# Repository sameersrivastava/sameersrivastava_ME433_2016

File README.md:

# sameersrivastava_ME433_2016
ME 433 Github Repository

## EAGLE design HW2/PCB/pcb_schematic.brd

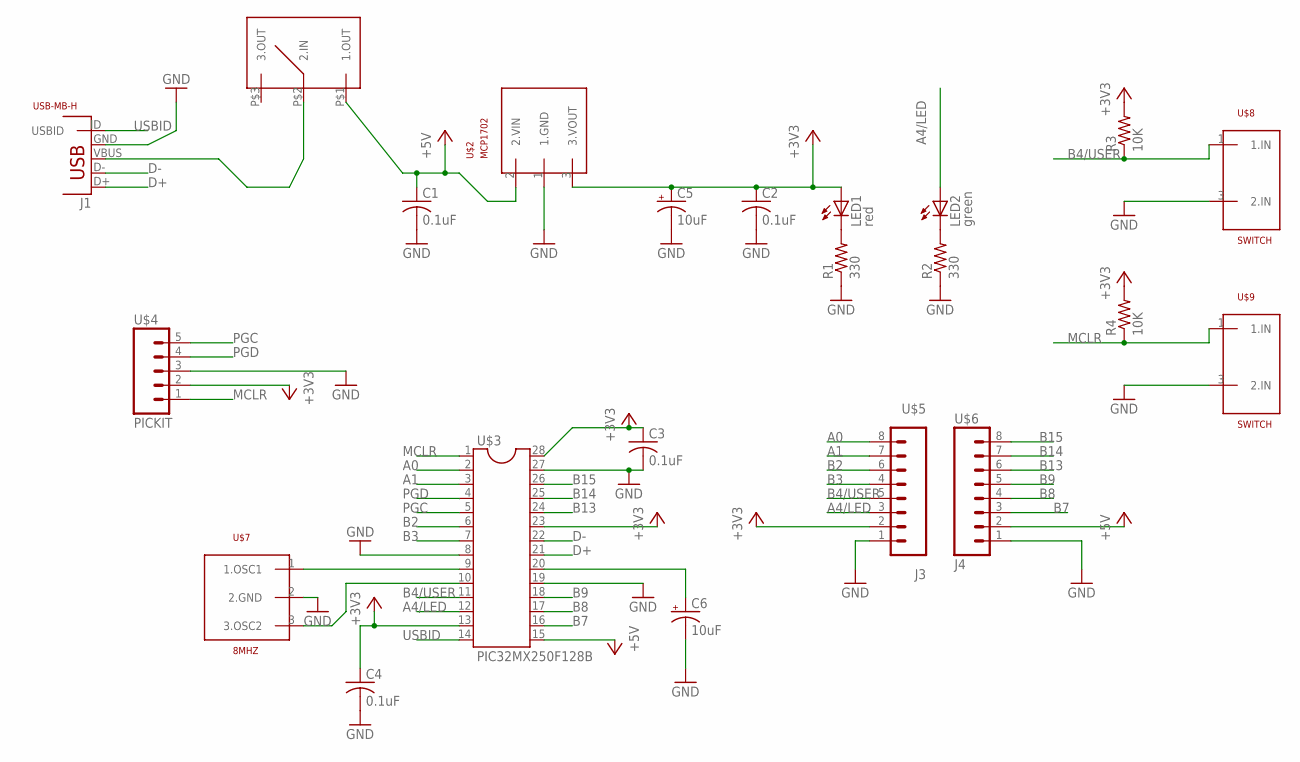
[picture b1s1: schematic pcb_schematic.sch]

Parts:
C1, C2, C3, C4: 0.1uF; C025-025X050
C5, C6: 10uF; B45181A
J1: USB-MB-H
LED1: red; LED3MM
LED2: green; LED3MM
R1, R2: 330; 0204/7
R3, R4: 10K; 0204/7
U$1: SLIDE_SWITCH
U$2: MCP1702; TO92
U$3: PIC32MX250F128B
U$4: PICKIT
U$5: J3
U$6: J4
U$7: 8MHZ
U$8, U$9: SWITCH

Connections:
+3V3: C2.1, C3.1, C4.1, C5.+, LED1.A, R3.2, R4.2, U$2.3 (3.VOUT), U$3.13 (13.VDD), U$3.23 (23.VUSB3V3), U$3.28 (28.AVDD), U$4.2 (2.3V3), U$5.2 (2.3V3)
+5V: C1.1, U$1.P$1 (1.OUT), U$2.2 (2.VIN), U$3.15 (15.VBUS), U$6.2 (2.5V)
A0: U$3.2 (2.A0), U$5.8 (8.A0)
A1: U$3.3 (3.A1), U$5.7 (7.A1)
A4/LED: LED2.A, U$3.12 (12.A4/LED), U$5.3 (3.A4/LED)
B2: U$3.6 (6.B2), U$5.6 (5.B3)
B3: U$3.7 (7.B3), U$5.4 (4.B4/USER)
B4/USER: R3.1, U$3.11 (11.B4/USER), U$5.5, U$8.1 (1.IN)
B7: U$3.16 (16.B7), U$6.3 (3.B7)
B8: U$3.17 (17.B8), U$6.4 (4.B8)
B9: U$3.18 (18.B9), U$6.5 (5.B9)
B13: U$3.24 (24.B13), U$6.6 (6.B13)
B14: U$3.25 (25.B14), U$6.7 (7.B14)
B15: U$3.26 (26.B15), U$6.8 (8.B15)
D+: J1.D+, U$3.21 (21.D+/B10)
D-: J1.D-, U$3.22 (22.D-/B11)
GND: C1.2, C2.2, C3.2, C4.2, C5.-, C6.-, J1.GND, R1.1, R2.1, U$2.1 (1.GND), U$3.8 (8.GND), U$3.19 (19.VSS), U$3.27 (27.AVSS), U$4.3 (3.GND), U$5.1 (1.GND), U$6.1 (1.GND), U$7.2 (2.GND), U$8.3 (2.IN), U$9.3 (2.IN)
MCLR: R4.1, U$3.1 (1.MCLR), U$4.1 (1.MCLR), U$9.1 (1.IN)
unnamed: J1.VBUS, U$1.P$2 (2.IN)
unnamed: LED1.K (C), R1.2
unnamed: LED2.K (C), R2.2
unnamed: U$3.9 (9.OSC1), U$7.1 (1.OSC1)
unnamed: U$3.10 (10.OSC2), U$7.3 (3.OSC2)
unnamed: C6.+, U$3.20 (20.VCAP)
PGC: U$3.5 (5.PGC), U$4.5 (5.PGC)
PGD: U$3.4 (4.PGD), U$4.4 (4.PGD)
USBID: J1.ID (USBID), U$3.14 (14.USBID/B5)

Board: 2 copper layers, 22 parts (0 on the bottom side), 27 nets, no tracks yet.

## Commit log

2016-04-05 Adding first commit of HW1 project with main.c
2016-04-05 .gitignore to .DS_Store. Moved HW1.X into HW1. Added a picture of the circuit diagram as well.
2016-04-05 Renamed circuit diagram to fit convention. Added picture of breadboard for number 6.
2016-04-07 Added oscillations for number 2 for hw1.
2016-04-07 Added schematic and library is mostly finished.
2016-04-12 Completed more components for the pic and added it to the library.
2016-04-14 Added the voltage regulator and the usb with the usbid pin connected to the library.
2016-04-14 Added PIC32 to the library.
2016-04-14 Added the 8MHz resonator
2016-04-14 Added the PICKit.
2016-04-14 Added J3 (The first set of connectors).
2016-04-14 Added J4 to the library now.
2016-04-14 Added the slide switch.
2016-04-14 Started the schematic. Do not have the buttons in the library.
2016-04-14 Started the schematic. Need to add nets.
2016-04-14 Finished a good bit of the schematic.
2016-04-14 Finished schematic minus the buttons. Not sure what to do about those still.
2016-04-14 Started board.
2016-04-16 more schematic stuff here.
2016-04-16 Fixed pragma values in main.c
2016-04-16 Fixed pragma values to correct values.
2016-04-16 Made B4 into an input for button and A4 into ouput for LED.
2016-04-16 Added code to switch between LED on and off for 0.5ms
2016-04-16 Added button input to pause the program.
2016-04-21 PCB is closer.
2016-04-28 Just updating things.
2016-04-28 Added project HW4.
2016-04-28 Took spi-example and put it into main.c
2016-05-03 Added PIC32.h file to have all the configurations for the PIC32.h
2016-05-03 Added PIC32.h to the main.c and worked fine. Started to rewrite functions to communicate over SPI1.
2016-05-03 Added setVoltage function, but need to check if this works. working on the main function.
2016-05-03 Got a successful compile on to the PIC.
2016-05-05 Just committing some automatic changes from MPLAB IDE.
2016-05-05 Starting Project 5. Added the LCD programs.
2016-05-05 Added the initialization steps, but nothing is working as of now.
2016-05-05 got something to work....
2016-05-05 Added a line.
2016-05-05 Getting closer.
2016-05-05 working
2016-05-05 Got it to print the hwk.
2016-05-05 Picture of hwk.
2016-05-10 Can write continous text to the screen for HW5.
2016-05-10 Started HW6/=.
2016-05-12 Got LCD to work for HW6. Now need to read gyrodata.
2016-05-12 Tried to communicate over I2C. Need to debug more.
2016-05-17 Made an initial android application.
2016-05-19 added mplab x properities.
2016-05-19 Did HW9 with the slider.
2016-05-19 Started HW12.
2016-05-19 Did initial working version of HW12.
2016-05-24 Added wheel part.
2016-05-31 Read WHOAMI register correctly :)
2016-05-31 reads temperature, but needs to be shortened.
2016-05-31 It is working. Not sure if the values are scaled correctly.
2016-06-02 Got the hdi_mouse to work.
2016-06-02 Got USB CDC to work
2016-06-04 Started HW13 and fixed more of HW 8. Can send any data back.
2016-06-04 Working version before lots of changes.
2016-06-04 Sending communication works over the PIC.Going to start trying to send more data.
2016-06-04 Screen does not turn off now.
2016-06-07 just committing code.
2016-06-07 Added the redraw for pixels.
2016-06-07 Added Seekbar to adjust threshold.
2016-06-07 Improved debugging for app.
2016-06-07 Good enough thresholding for now.
2016-06-07 Working version right now. Trying to send over more data.
2016-06-07 Can read integers for CDC from PIC.
2016-06-07 Got code to work on one motor. Not sure why both are not working right now.
2016-06-07 Got PWM to work somehow..
2016-06-07 Can write to PICgit status
2016-06-07 Did not break with new layout.
2016-06-07 Apps are almost combined.
2016-06-10 Finished HW16.
2016-06-10 Added HW15 and HW14.
2016-06-10 Added more stuff.
2016-07-08 Going to delete local copy of repo, but commiting last bit of code to origin.:
